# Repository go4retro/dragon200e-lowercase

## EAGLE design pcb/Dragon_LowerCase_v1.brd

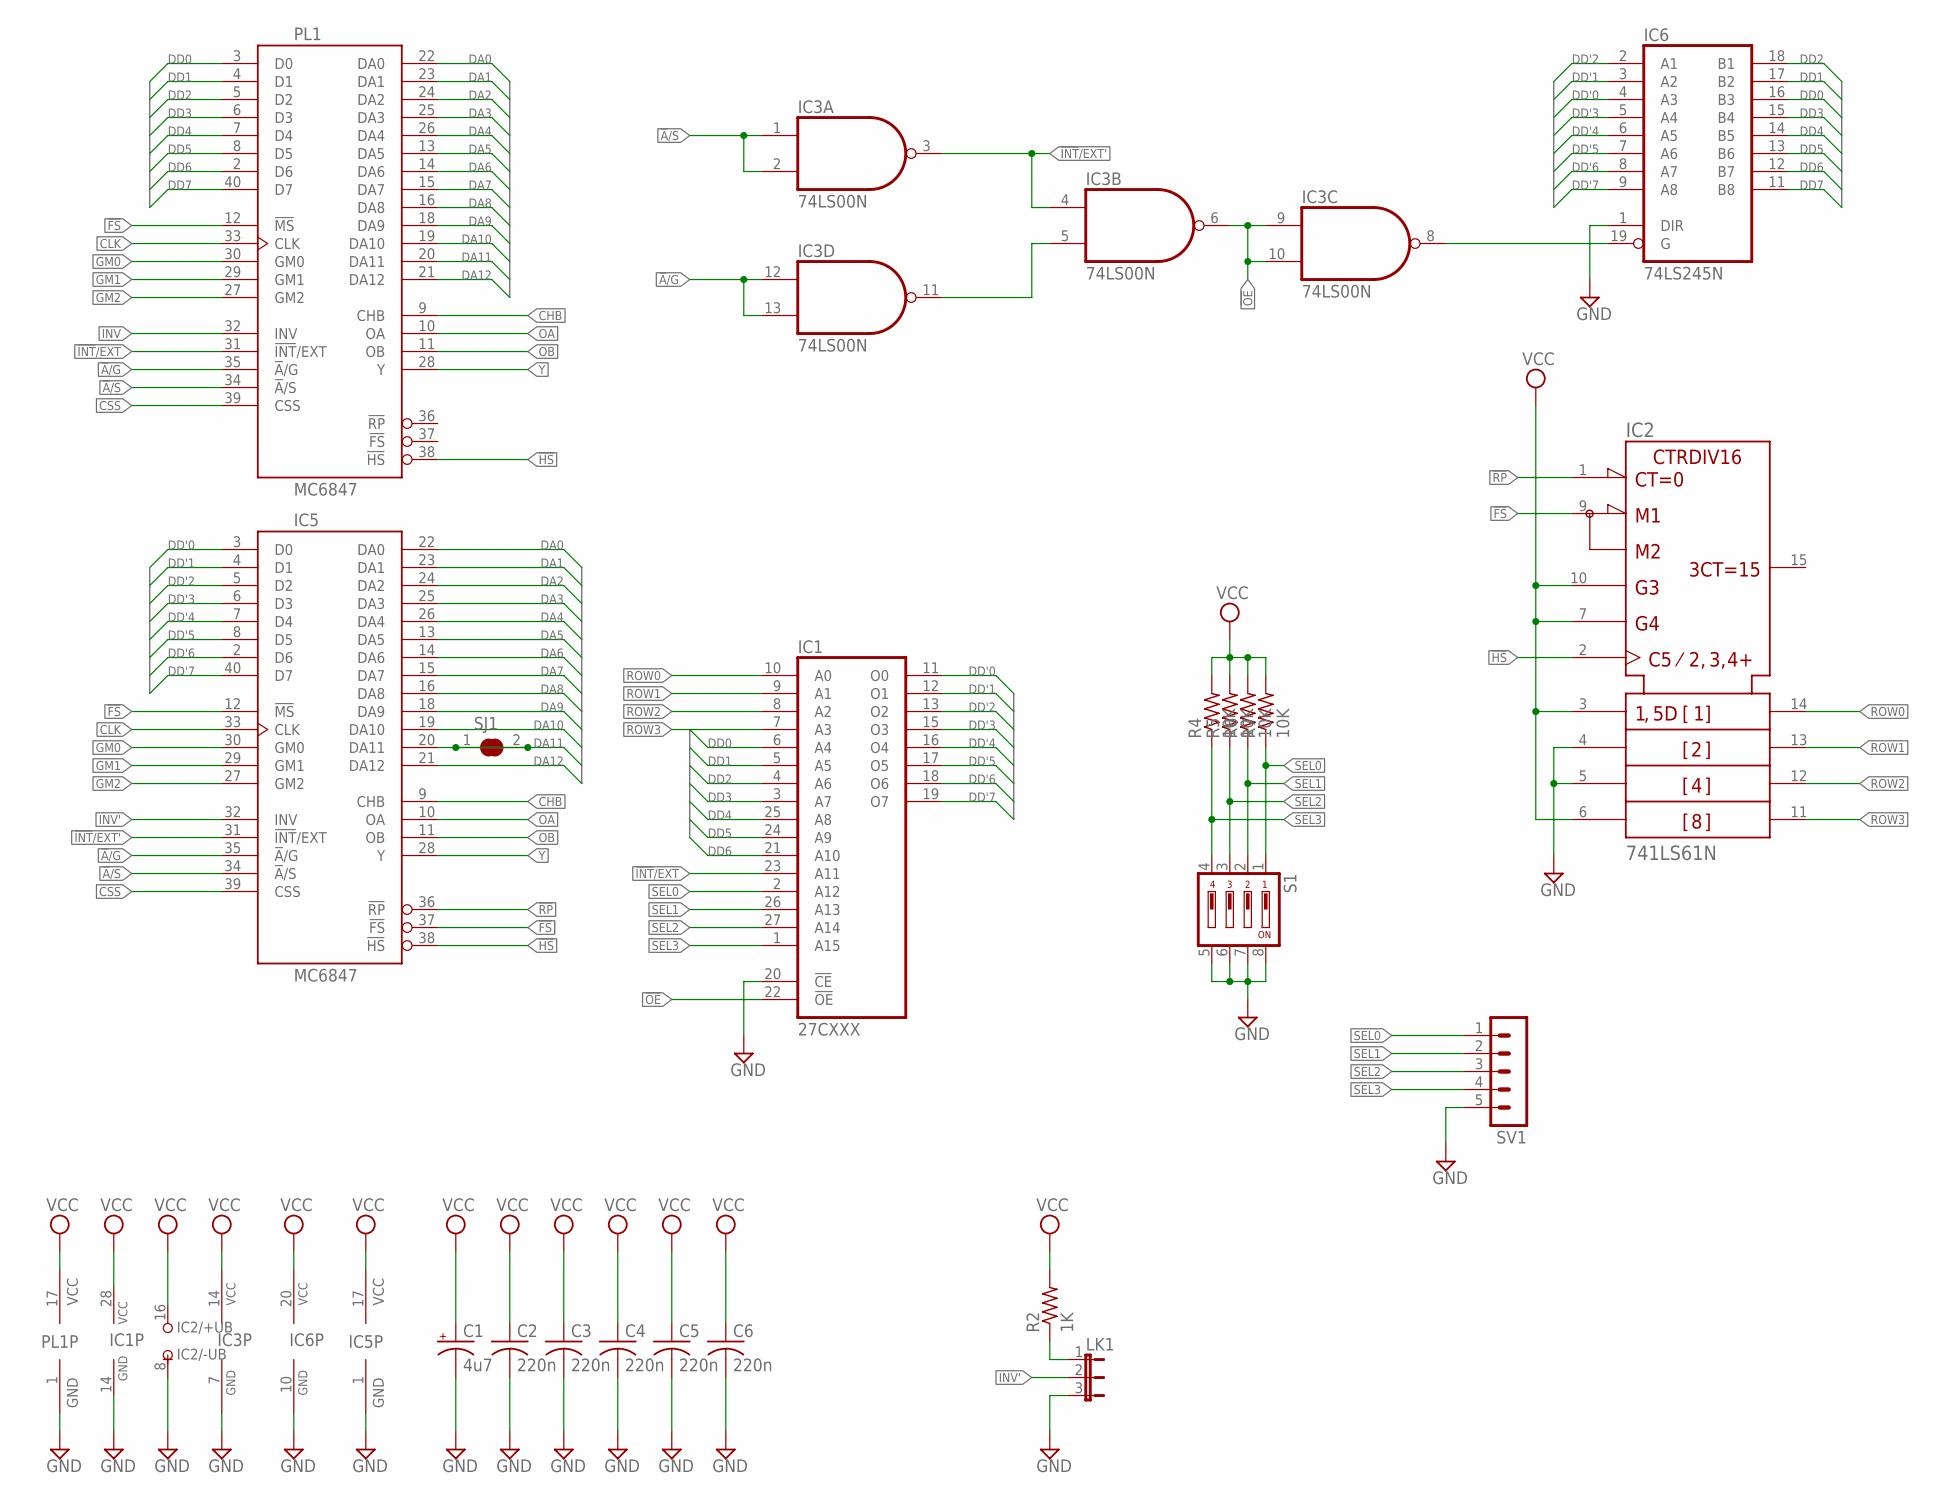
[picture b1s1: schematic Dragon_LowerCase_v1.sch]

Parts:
C1: 4u7; E2,5-5
C2, C3, C4, C6: 220n; C025-025X050
C5: 220n; C050-025X075
IC1: 27CXXX; DIL28
IC2: 741LS61N; DIL16
IC3: 74LS00N; DIL14-RP
IC5: MC6847; DIL40
IC6: 74LS245N; DIL20-RP
LK1: JP2E; JP2
PL1: MC6847; DIL40
R2: 1K; 0204V
R4, R5, R6, R7: 10K; 0204V
S1: DS04; DS-04
SJ1: SJ
SV1: MA05-1

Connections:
!A!/G: IC3.12 (I0), IC3.13 (I1), IC5.35 (!A!/G), PL1.35 (!A!/G)
!A!/S: IC3.1 (I0), IC3.2 (I1), IC5.34 (!A!/S), PL1.34 (!A!/S)
!FS: IC2.9 (!LOAD), IC5.12 (!MS), IC5.37 (!FS), PL1.12 (!MS)
!HS: IC2.2 (CLK), IC5.38 (!HS), PL1.38 (!HS)
!INT!/EXT: IC1.23 (A11), PL1.31 (!INT!/EXT)
!INT!/EXT': IC3.3 (O), IC3.4 (I0), IC5.31 (!INT!/EXT)
!OE: IC1.22 (!OE), IC3.6 (O), IC3.9 (I0), IC3.10 (I1)
!RP: IC2.1 (!CLR), IC5.36 (!RP)
CHB: IC5.9 (CHB), PL1.9 (CHB)
CLK: IC5.33 (CLK), PL1.33 (CLK)
CSS: IC5.39 (CSS), PL1.39 (CSS)
DA0: IC5.22 (DA0), PL1.22 (DA0)
DA1: IC5.23 (DA1), PL1.23 (DA1)
DA2: IC5.24 (DA2), PL1.24 (DA2)
DA3: IC5.25 (DA3), PL1.25 (DA3)
DA4: IC5.26 (DA4), PL1.26 (DA4)
DA5: IC5.13 (DA5), PL1.13 (DA5)
DA6: IC5.14 (DA6), PL1.14 (DA6)
DA7: IC5.15 (DA7), PL1.15 (DA7)
DA8: IC5.16 (DA8), PL1.16 (DA8)
DA9: IC5.18 (DA9), PL1.18 (DA9)
DA10: IC5.19 (DA10), PL1.19 (DA10)
DA11: IC5.20 (DA11), PL1.20 (DA11), SJ1.1, SJ1.2
DA12: IC5.21 (DA12), PL1.21 (DA12)
DD0: IC1.6 (A4), IC6.16 (B3), PL1.3 (D0)
DD1: IC1.5 (A5), IC6.17 (B2), PL1.4 (D1)
DD2: IC1.4 (A6), IC6.18 (B1), PL1.5 (D2)
DD3: IC1.3 (A7), IC6.15 (B4), PL1.6 (D3)
DD4: IC1.25 (A8), IC6.14 (B5), PL1.7 (D4)
DD5: IC1.24 (A9), IC6.13 (B6), PL1.8 (D5)
DD6: IC1.21 (A10), IC6.12 (B7), PL1.2 (D6)
DD7: IC6.11 (B8), PL1.40 (D7)
DD'0: IC1.11 (O0), IC5.3 (D0), IC6.4 (A3)
DD'1: IC1.12 (O1), IC5.4 (D1), IC6.3 (A2)
DD'2: IC1.13 (O2), IC5.5 (D2), IC6.2 (A1)
DD'3: IC1.15 (O3), IC5.6 (D3), IC6.5 (A4)
DD'4: IC1.16 (O4), IC5.7 (D4), IC6.6 (A5)
DD'5: IC1.17 (O5), IC5.8 (D5), IC6.7 (A6)
DD'6: IC1.18 (O6), IC5.2 (D6), IC6.8 (A7)
DD'7: IC1.19 (O7), IC5.40 (D7), IC6.9 (A8)
GM0: IC5.30 (GM0), PL1.30 (GM0)
GM1: IC5.29 (GM1), PL1.29 (GM1)
GM2: IC5.27 (GM2), PL1.27 (GM2)
GND: C1.-, C2.2, C3.2, C4.2, C5.2, C6.2, IC1.14 (GND), IC1.20 (!CE), IC2.4 (B), IC2.5 (C), IC2.8 (-UB), IC3.7 (GND), IC5.1 (GND), IC6.1 (DIR), IC6.10 (GND), LK1.3, PL1.1 (GND), S1.5, S1.6, S1.7, S1.8, SV1.5
INV: PL1.32 (INV)
INV': IC5.32 (INV), LK1.2
unnamed: LK1.1, R2.1
unnamed: IC3.8 (O), IC6.19 (G)
unnamed: IC3.5 (I1), IC3.11 (O)
OA: IC5.10 (OA), PL1.10 (OA)
OB: IC5.11 (OB), PL1.11 (OB)
ROW0: IC1.10 (A0), IC2.14 (QA)
ROW1: IC1.9 (A1), IC2.13 (QB)
ROW2: IC1.8 (A2), IC2.12 (QC)
ROW3: IC1.7 (A3), IC2.11 (QD)
SEL0: IC1.2 (A12), R7.1, S1.1, SV1.1
SEL1: IC1.26 (A13), R6.1, S1.2, SV1.2
SEL2: IC1.27 (A14), R5.1, S1.3, SV1.3
SEL3: IC1.1 (A15), R4.1, S1.4, SV1.4
VCC: C1.+, C2.1, C3.1, C4.1, C5.1, C6.1, IC1.28 (VCC), IC2.3 (A), IC2.6 (D), IC2.7 (ENP), IC2.10 (ENT), IC2.16 (+UB), IC3.14 (VCC), IC5.17 (VCC), IC6.20 (VCC), PL1.17 (VCC), R2.2, R4.2, R5.2, R6.2, R7.2
Y: IC5.28 (Y), PL1.28 (Y)

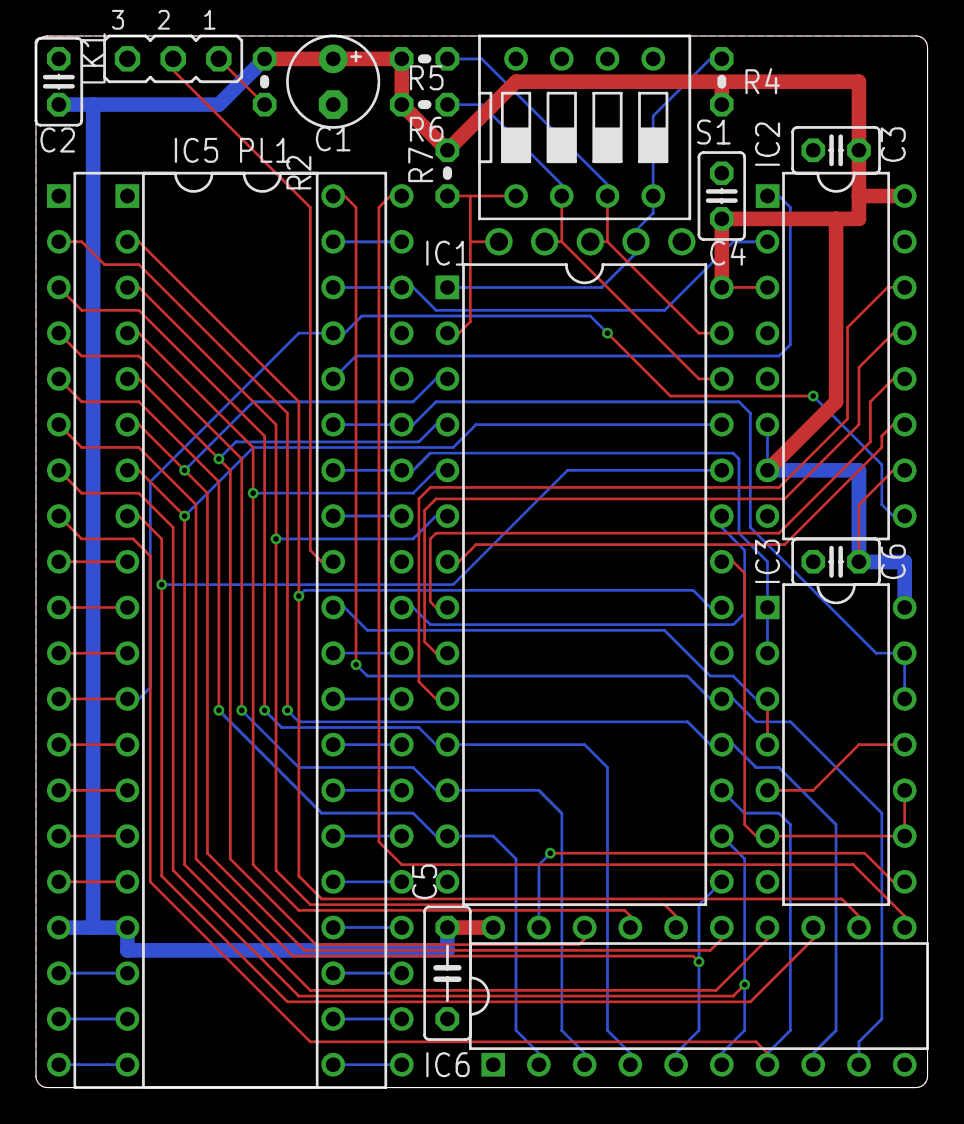
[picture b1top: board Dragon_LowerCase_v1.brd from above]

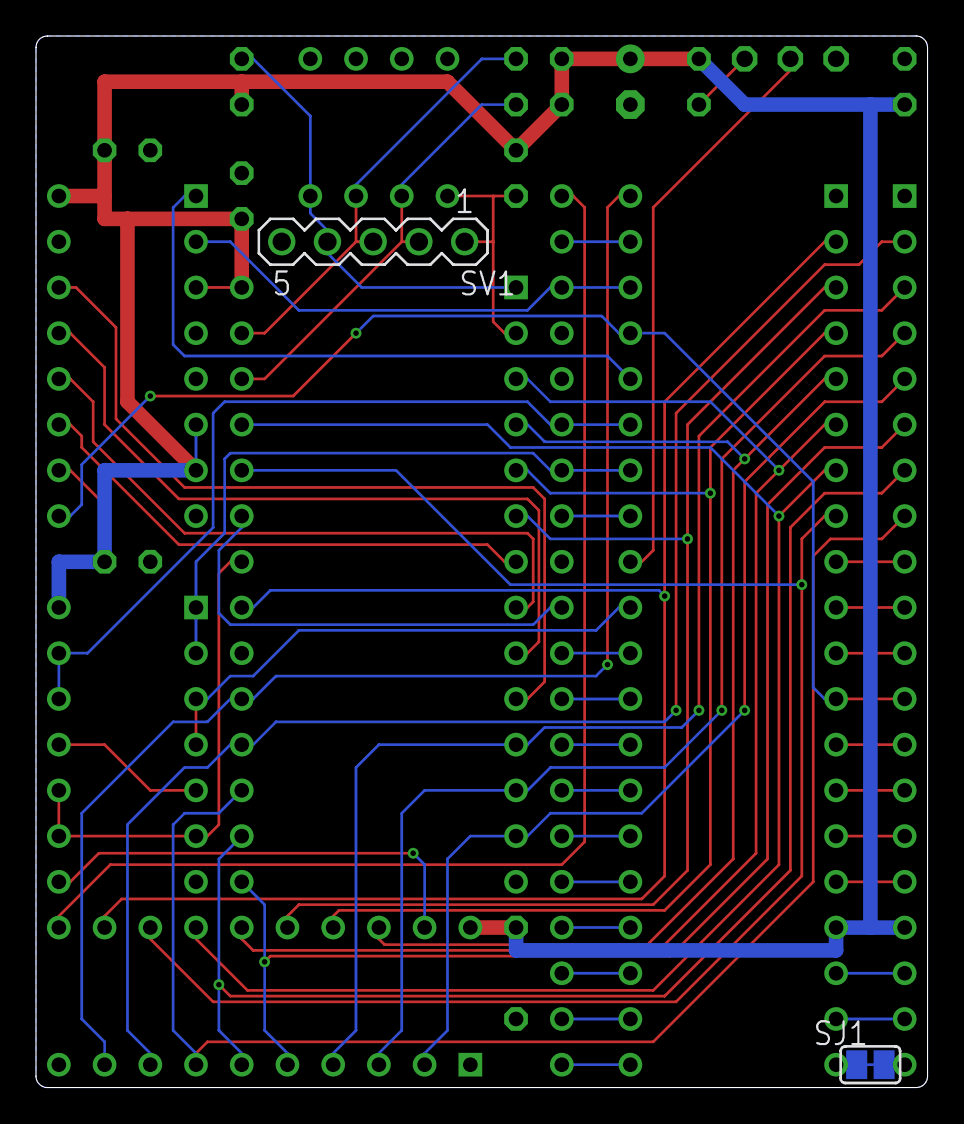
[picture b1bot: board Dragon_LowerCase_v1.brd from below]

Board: 2 copper layers, 49.5 x 58.4 mm, 21 parts (2 on the bottom side), 60 nets.

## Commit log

2024-11-05 Adding in original Dragon 200e ROM dump
2024-11-05 Added README in charsets dir
2024-11-05 README updates
2024-11-10 Added initial reverse engineering of PCB
2024-11-17 Shrink PCB and update EPROM. Add in reference data
